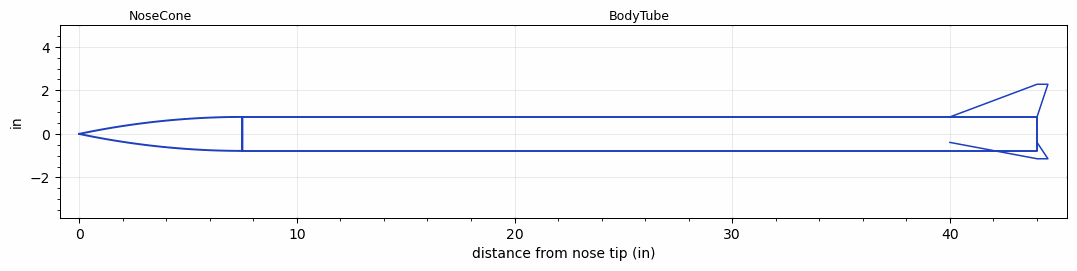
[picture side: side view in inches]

<RASAeroDocument>
 <FileVersion>2</FileVersion>
 <RocketDesign>
  <NoseCone>
   <Length>7.5</Length>
   <Diameter>1.56</Diameter>
   <Shape>Tangent Ogive</Shape>
   <Location>0</Location>
  </NoseCone>
  <BodyTube>
   <Length>36.5</Length>
   <Diameter>1.56</Diameter>
   <Location>7.5</Location>
   <Fin>
    <Count>3</Count>
    <Chord>4</Chord>
    <Span>1.5</Span>
    <SweepDistance>4</SweepDistance>
    <TipChord>0.5</TipChord>
    <Thickness>0.125</Thickness>
    <LERadius>0.02</LERadius>
    <Location>4</Location>
    <AirfoilSection>Hexagonal</AirfoilSection>
    <FX1>0.25</FX1>
    <FX3>0.25</FX3>
   </Fin>
  </BodyTube>
  <Surface>Rough Camouflage Paint</Surface>
  <ModifiedBarrowman>True</ModifiedBarrowman>
  <Turbulence>True</Turbulence>
  <UseBooster1>False</UseBooster1>
  <UseBooster2>False</UseBooster2>
 </RocketDesign>
 <LaunchSite>
  <Altitude>1000</Altitude>
  <Pressure>0</Pressure>
  <RodAngle>3</RodAngle>
  <RodLength>6</RodLength>
  <Temperature>74</Temperature>
  <WindSpeed>10</WindSpeed>
 </LaunchSite>
 <Recovery>
  <Altitude1>1000</Altitude1>
  <Altitude2>500</Altitude2>
  <DeviceType1>Parachute</DeviceType1>
  <DeviceType2>Parachute</DeviceType2>
  <Event1>True</Event1>
  <Event2>True</Event2>
  <Size1>9</Size1>
  <Size2>30</Size2>
  <EventType1>Apogee</EventType1>
  <EventType2>Altitude</EventType2>
  <CD1>1.33</CD1>
  <CD2>1.33</CD2>
 </Recovery>
 <SimulationList>
  <Simulation>
   <SustainerEngine>J530-IM  (CTI)</SustainerEngine>
   <SustainerLaunchWt>4.87</SustainerLaunchWt>
   <SustainerCG>25.24</SustainerCG>
   <SustainerIgnitionDelay>0</SustainerIgnitionDelay>
   <Booster1SeparationDelay>0</Booster1SeparationDelay>
   <Booster1IgnitionDelay>0</Booster1IgnitionDelay>
   <IncludeBooster1>False</IncludeBooster1>
   <Booster2Delay>0</Booster2Delay>
   <IncludeBooster2>False</IncludeBooster2>
   <TimetoApogee>26.81052</TimetoApogee>
   <MaxAltitude>15050.03</MaxAltitude>
   <MaxVelocity>1649.232</MaxVelocity>
   <OptimumWt>3.896001</OptimumWt>
   <OptimumMaxAlt>3.896001</OptimumMaxAlt>
  </Simulation>
  <Simulation>
   <SustainerEngine>I540WT  (CTI)</SustainerEngine>
   <SustainerLaunchWt>4.25</SustainerLaunchWt>
   <SustainerCG>24.65</SustainerCG>
   <SustainerIgnitionDelay>0</SustainerIgnitionDelay>
   <Booster1SeparationDelay>0</Booster1SeparationDelay>
   <Booster1IgnitionDelay>0</Booster1IgnitionDelay>
   <IncludeBooster1>False</IncludeBooster1>
   <Booster2Delay>0</Booster2Delay>
   <IncludeBooster2>False</IncludeBooster2>
   <TimetoApogee>22.22041</TimetoApogee>
   <MaxAltitude>9424.86</MaxAltitude>
   <MaxVelocity>1100.517</MaxVelocity>
  </Simulation>
  <Simulation>
   <SustainerEngine>J500G  (AT)</SustainerEngine>
   <SustainerLaunchWt>3.55</SustainerLaunchWt>
   <SustainerCG>25.31</SustainerCG>
   <SustainerIgnitionDelay>0</SustainerIgnitionDelay>
   <Booster1SeparationDelay>0</Booster1SeparationDelay>
   <Booster1IgnitionDelay>0</Booster1IgnitionDelay>
   <IncludeBooster1>False</IncludeBooster1>
   <Booster2Delay>0</Booster2Delay>
   <IncludeBooster2>False</IncludeBooster2>
   <TimetoApogee>22.93043</TimetoApogee>
   <MaxAltitude>11239.04</MaxAltitude>
   <MaxVelocity>1464.661</MaxVelocity>
  </Simulation>
  <Simulation>
   <SustainerEngine>I1299N  (AT)</SustainerEngine>
   <SustainerLaunchWt>3.63</SustainerLaunchWt>
   <SustainerCG>23.46</SustainerCG>
   <SustainerIgnitionDelay>0</SustainerIgnitionDelay>
   <Booster1SeparationDelay>0</Booster1SeparationDelay>
   <Booster1IgnitionDelay>0</Booster1IgnitionDelay>
   <IncludeBooster1>False</IncludeBooster1>
   <Booster2Delay>0</Booster2Delay>
   <IncludeBooster2>False</IncludeBooster2>
   <TimetoApogee>18.63033</TimetoApogee>
   <MaxAltitude>6588.021</MaxAltitude>
   <MaxVelocity>875.6287</MaxVelocity>
  </Simulation>
 </SimulationList>
</RASAeroDocument>
